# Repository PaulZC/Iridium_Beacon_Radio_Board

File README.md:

# Iridium 9603N Beacon Radio Board

A radio board for the [Iridium 9603N Beacon](https://github.com/PaulZC/Iridium_9603_Beacon). Equipped with an
[LPRS eRIC4 or eRIC9 integrated radio module](http://www.lprs.co.uk/products/easyradio-ism-modules/eric-soc-rf-modules.html),
this board allows remote control of radio-enabled devices near the Iridium Beacon. E.g. a
[radio-enabled cut-down device](https://github.com/PaulZC/Pyrotechnic_Balloon_Cut-Down).

See [ASSEMBLY.md](https://github.com/PaulZC/Iridium_Beacon_Radio_Board/blob/master/ASSEMBLY.md) for details on how to assemble the PCB.

See [Iridium_Beacon_Radio_Board_V1.pdf](https://github.com/PaulZC/Iridium_Beacon_Radio_Board/blob/master/Iridium_Beacon_Radio_Board_V1.pdf) for the schematic,
layout and Bill Of Materials.

The [Eagle](https://github.com/PaulZC/Iridium_Beacon_Radio_Board/tree/master/Eagle) directory contains the schematic and pcb design files.

### License

This project is distributed under a Creative Commons Attribution + Share-alike (BY-SA) licence.
Please refer to section 5 of the licence for the Disclaimer of Warranties and Limitation of Liability.

Enjoy!

**_Paul_**

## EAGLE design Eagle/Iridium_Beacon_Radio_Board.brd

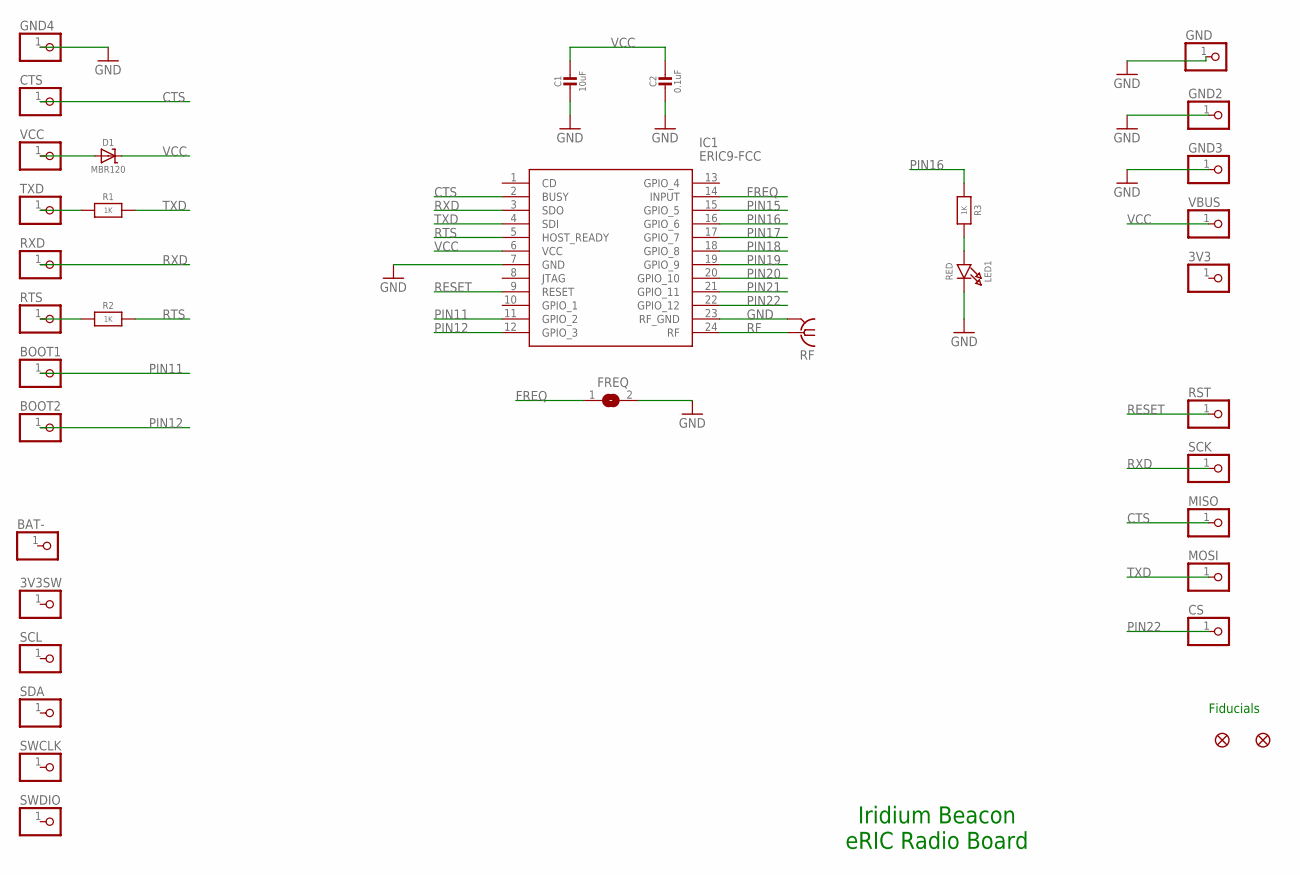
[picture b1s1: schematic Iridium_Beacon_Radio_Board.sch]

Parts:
3V3, 3V3SW: PINHD-1X1; 1X01
BAT-: PINHD-1X1; 1X01
BOOT1, BOOT2: PINHD-1X1; 1X01
C1: 10uF; 0805-NO
C2: 0.1uF; 0603-NO
CS: PINHD-1X1; 1X01
CTS: PINHD-1X1; 1X01
D1: MBR120; SOD-123
FD1, FD2: FIDUCIAL1X2; FIDUCIAL-1X2
FREQ: SOLDERJUMPER; SOLDERJUMPER_ARROW_NOPASTE
GND, GND2, GND3, GND4: PINHD-1X1; 1X01
IC1: ERIC9-FCC; ERIC4
LED1: RED; CHIPLED_0805_NOOUTLINE
MISO: PINHD-1X1; 1X01
MOSI: PINHD-1X1; 1X01
R1, R2, R3: 1K; 0603-NO
RF: SMA-142-0711-821/826; J502-ND-142-0711-821/826
RST: PINHD-1X1; 1X01
RTS: PINHD-1X1; 1X01
RXD: PINHD-1X1; 1X01
SCK: PINHD-1X1; 1X01
SCL: PINHD-1X1; 1X01
SDA: PINHD-1X1; 1X01
SWCLK: PINHD-1X1; 1X01
SWDIO: PINHD-1X1; 1X01
TXD: PINHD-1X1; 1X01
VBUS: PINHD-1X1; 1X01
VCC: PINHD-1X1; 1X01

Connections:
CTS: CTS.1, IC1.2 (BUSY), MISO.1
FREQ: FREQ.1, IC1.14 (INPUT)
GND: C1.2, C2.2, FREQ.2, GND.1, GND2.1, GND3.1, GND4.1, IC1.7 (GND), IC1.23 (RF_GND), LED1.C, RF.G@1 (2), RF.G@2 (2), RF.G@3 (2), RF.G@4 (2)
unnamed: LED1.A, R3.2
unnamed: R1.1, TXD.1
unnamed: R2.1, RTS.1
unnamed: D1.A, VCC.1
PIN11: BOOT1.1, IC1.11 (GPIO_2)
PIN12: BOOT2.1, IC1.12 (GPIO_3)
PIN15: IC1.15 (GPIO_5)
PIN16: IC1.16 (GPIO_6), R3.1
PIN17: IC1.17 (GPIO_7)
PIN18: IC1.18 (GPIO_8)
PIN19: IC1.19 (GPIO_9)
PIN20: IC1.20 (GPIO_10)
PIN21: IC1.21 (GPIO_11)
PIN22: CS.1, IC1.22 (GPIO_12)
RESET: IC1.9 (RESET), RST.1
RF: IC1.24 (RF), RF.1
RTS: IC1.5 (HOST_READY), R2.2
RXD: IC1.3 (SDO), RXD.1, SCK.1
TXD: IC1.4 (SDI), MOSI.1, R1.2
VCC: C1.1, C2.1, D1.C, IC1.6 (VCC), VBUS.1

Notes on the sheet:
Iridium Beacon eRIC Radio Board
Fiducials

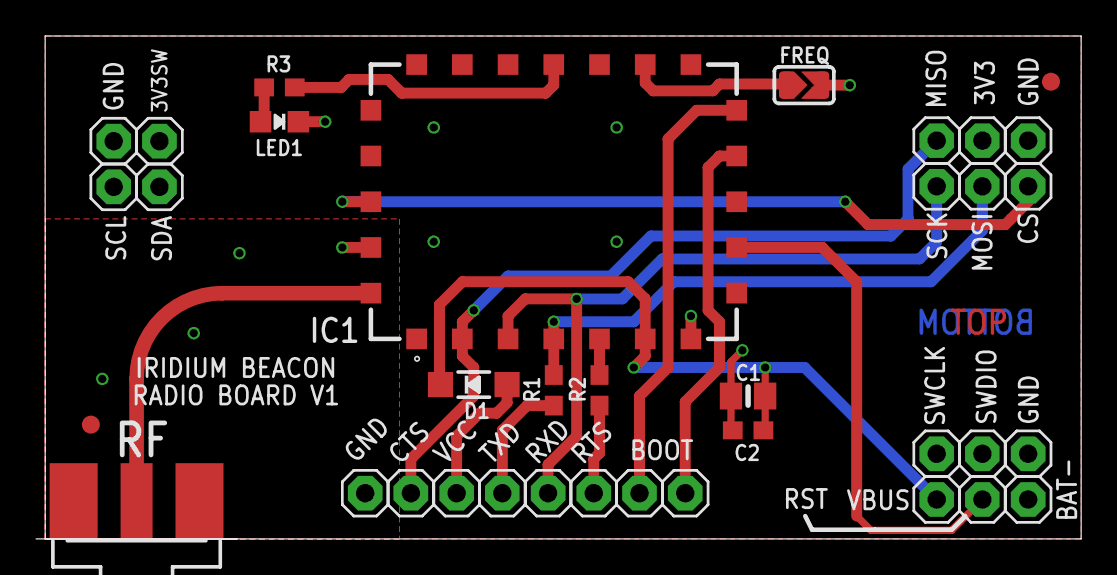
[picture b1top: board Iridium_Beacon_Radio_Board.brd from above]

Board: 2 copper layers, 58.1 x 27.9 mm, 36 parts (0 on the bottom side), 17 nets.

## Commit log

2018-09-24 First release
2018-09-24 Corrected a typo
2018-09-29 Added weight info

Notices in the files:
parts and their libraries:
microbuilder: This work is placed in the public domain, and may be freely used for commercial and non-commercial work with the following conditions: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
SparkFun-Aesthetics: Licensing: Creative Commons ShareAlike 4.0 International - https://creativecommons.org/licenses/by-sa/4.0
